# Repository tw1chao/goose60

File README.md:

# goose60

goose60 是一個 60% 鍵盤 PCB 電路板專案。
設計目標是做出一把**無光害的熱插拔鍵盤**，MCU 採用 ARM Cortex-M3 的 STM32F103。所有按鍵位置皆支援軸體熱插拔，本系列含子專案皆為無光害版本，故電路上僅會有的 `caps lock` 指示燈。

goose60 支援標準60%布局，下面表格列出子專案及支援的布局。

| Sub-Project | Layout |
|-------------|--------|
| JY60        | HHKB   |
| Cattle60    | ISO    |

未來視情況需要，再新增其他布局的子專案。

## 3D 預覽

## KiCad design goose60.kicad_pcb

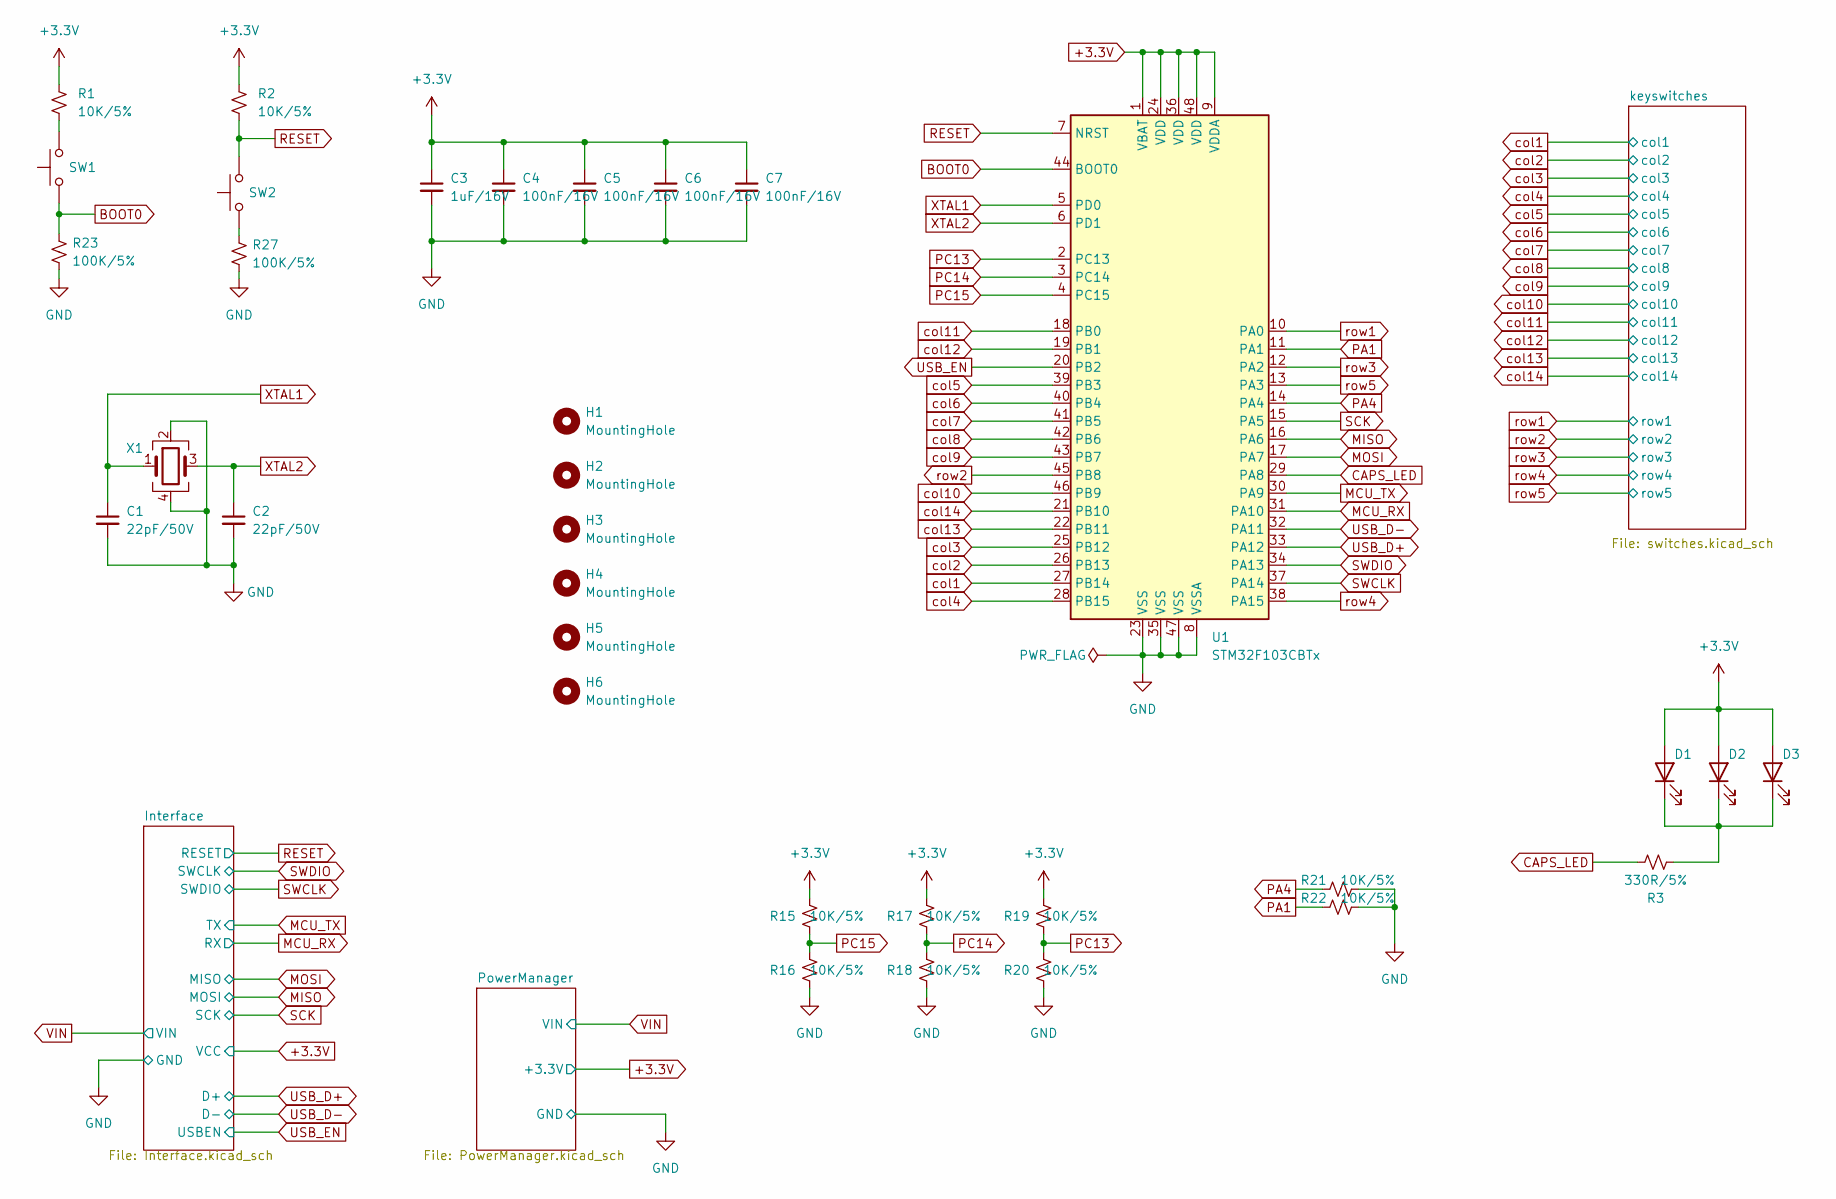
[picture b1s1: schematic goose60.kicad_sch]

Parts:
C1, C2: 22pF/50V; C_0603_1608Metric
C3: 1uF/16V; C_0603_1608Metric
C4, C5, C6, C7: 100nF/16V; C_0603_1608Metric
D1, D2, D3: LED; LED_0805_2012Metric
H1: MountingHole; MountingHole_3.2mm_M3_Pad
H2, H3, H4, H5, H6: MountingHole; MountingHole_3.2mm_M3_Pad_TopOnly
R1, R2, R15, R16, R17, R18, R19, R20, R21, R22: 10K/5%; R_0603_1608Metric
R3: 330R/5%; R_0603_1608Metric
R23, R27: 100K/5%; R_0603_1608Metric
SW1, SW2: SW_Push; SW_Push_1P1T_NO_CK_KSC6xxJ
U1: STM32F103CBTx; LQFP-48_7x7mm_P0.5mm
X1: Crystal_GND24; Crystal_SMD_TXC_7M-4Pin_3.2x2.5mm

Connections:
+3.3V: C3.1, C4.1, C5.1, C6.1, C7.1, D1.2 (A), D2.2 (A), D3.2 (A), R1.1, R2.1, R15.1, R17.1, R19.1, U1.1 (VBAT), U1.9 (VDDA), U1.24 (VDD), U1.36 (VDD), U1.48 (VDD); also elsewhere on the board
BOOT0: R23.1, SW1.1, U1.44 (BOOT0)
CAPS_LED: R3.2, U1.29 (PA8)
GND: C1.2, C2.2, C3.2, C4.2, C5.2, C6.2, C7.2, R16.2, R18.2, R20.2, R21.1, R22.1, R23.2, R27.2, U1.8 (VSSA), U1.23 (VSS), U1.35 (VSS), U1.47 (VSS), X1.2, X1.4; also elsewhere on the board
MCU_RX: U1.31 (PA10); also elsewhere on the board
MCU_TX: U1.30 (PA9); also elsewhere on the board
MISO: U1.16 (PA6); also elsewhere on the board
MOSI: U1.17 (PA7); also elsewhere on the board
unnamed: D1.1 (K), D2.1 (K), D3.1 (K), R3.1
unnamed: R1.2, SW1.2
unnamed: R27.1, SW2.1
PA1: R22.2, U1.11 (PA1)
PA4: R21.2, U1.14 (PA4)
PC13: R19.2, R20.1, U1.2 (PC13)
PC14: R17.2, R18.1, U1.3 (PC14)
PC15: R15.2, R16.1, U1.4 (PC15)
RESET: R2.2, SW2.2, U1.7 (NRST); also elsewhere on the board
SCK: U1.15 (PA5); also elsewhere on the board
SWCLK: U1.37 (PA14); also elsewhere on the board
SWDIO: U1.34 (PA13); also elsewhere on the board
USB_D+: U1.33 (PA12); also elsewhere on the board
USB_D-: U1.32 (PA11); also elsewhere on the board
USB_EN: U1.20 (PB2); also elsewhere on the board
XTAL1: C1.1, U1.5 (PD0), X1.1
XTAL2: C2.1, U1.6 (PD1), X1.3
col1: U1.27 (PB14); also elsewhere on the board
col2: U1.26 (PB13); also elsewhere on the board
col3: U1.25 (PB12); also elsewhere on the board
col4: U1.28 (PB15); also elsewhere on the board
col5: U1.39 (PB3); also elsewhere on the board
col6: U1.40 (PB4); also elsewhere on the board
col7: U1.41 (PB5); also elsewhere on the board
col8: U1.42 (PB6); also elsewhere on the board
col9: U1.43 (PB7); also elsewhere on the board
col10: U1.46 (PB9); also elsewhere on the board
col11: U1.18 (PB0); also elsewhere on the board
col12: U1.19 (PB1); also elsewhere on the board
col13: U1.22 (PB11); also elsewhere on the board
col14: U1.21 (PB10); also elsewhere on the board
row1: U1.10 (PA0); also elsewhere on the board
row2: U1.45 (PB8); also elsewhere on the board
row3: U1.12 (PA2); also elsewhere on the board
row4: U1.38 (PA15); also elsewhere on the board
row5: U1.13 (PA3); also elsewhere on the board

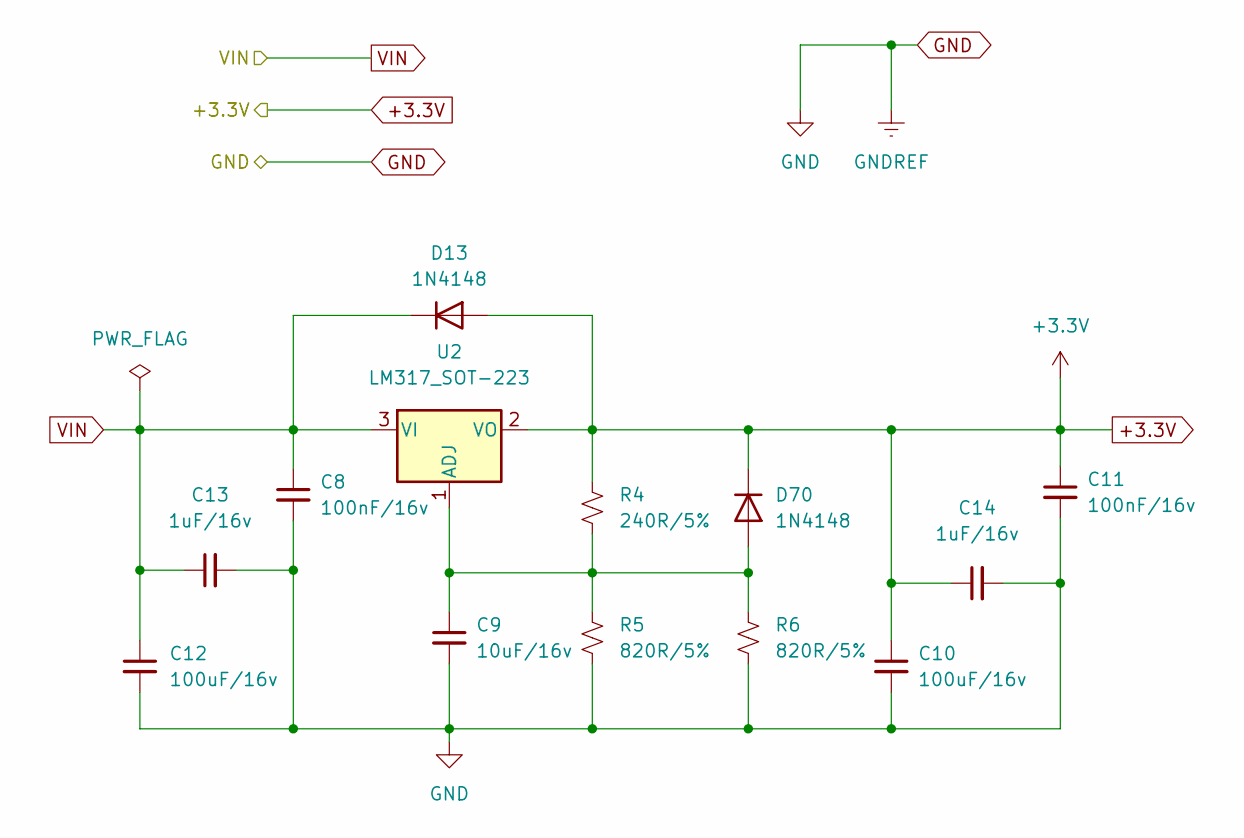
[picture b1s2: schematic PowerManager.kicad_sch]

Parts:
C8, C11: 100nF/16v; C_0603_1608Metric
C9: 10uF/16v; C_0805_2012Metric
C10, C12: 100uF/16v; C_1206_3216Metric
C13, C14: 1uF/16v; C_0603_1608Metric
D13, D70: 1N4148; D_0805_2012Metric
R4: 240R/5%; R_0603_1608Metric
R5, R6: 820R/5%; R_0603_1608Metric
U2: LM317_SOT-223; SOT-223-3_TabPin2

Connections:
+3.3V: C10.1, C11.1, C14.1, D13.2 (A), D70.1 (K), R4.1, U2.2 (VO); also elsewhere on the board
GND: C8.2, C9.2, C10.2, C11.2, C12.2, C13.2, C14.2, R5.2, R6.2; also elsewhere on the board
unnamed: C9.1, D70.2 (A), R4.2, R5.1, R6.1, U2.1 (ADJ)
VIN: C8.1, C12.1, C13.1, D13.1 (K), U2.3 (VI); also elsewhere on the board

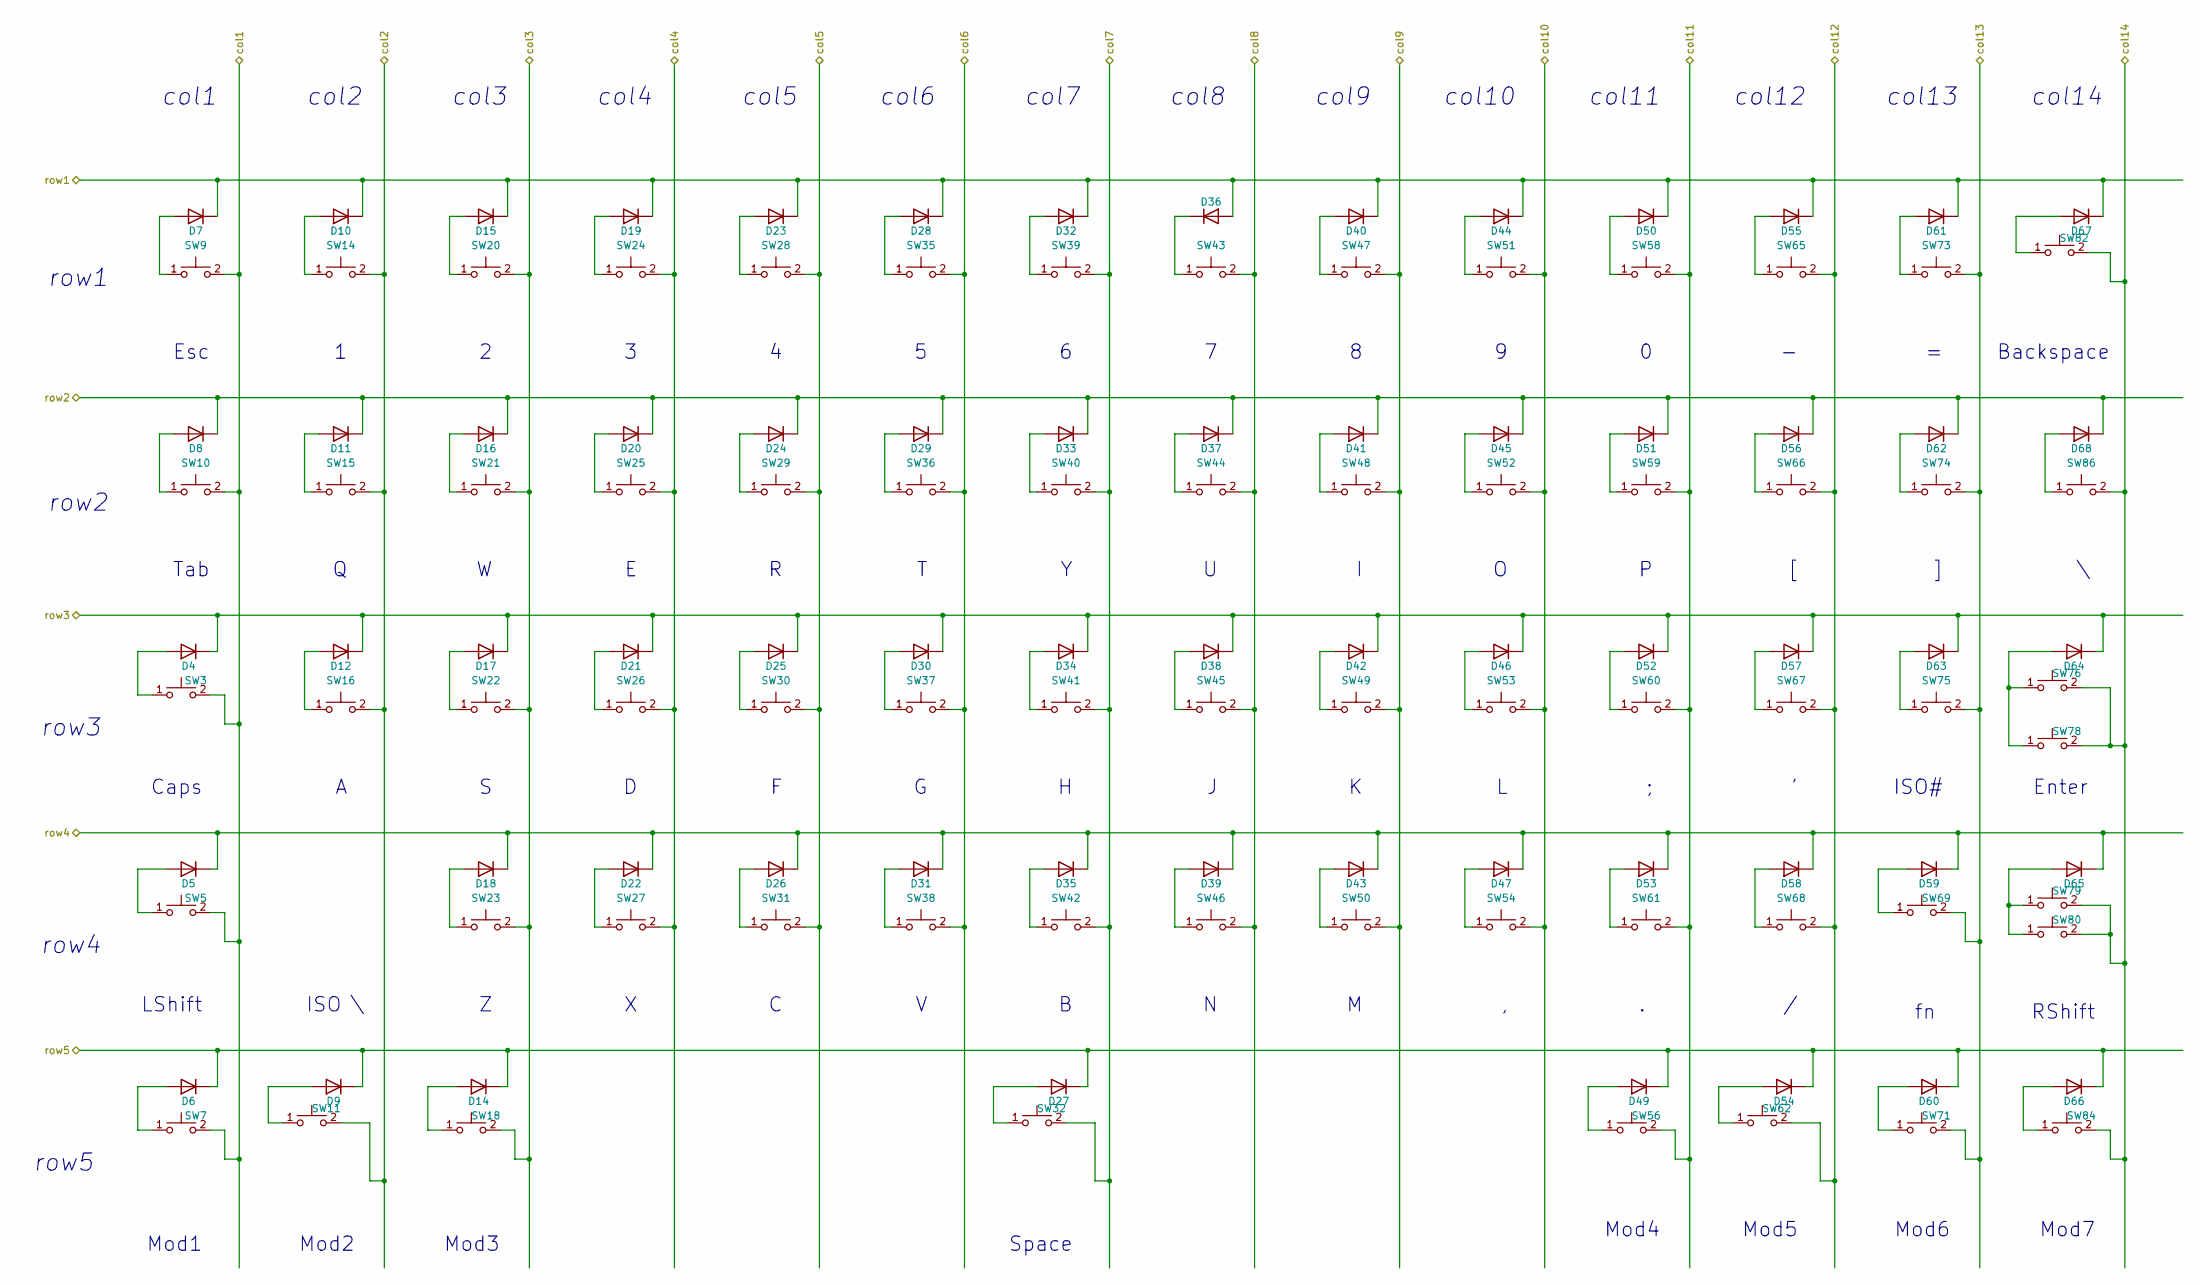
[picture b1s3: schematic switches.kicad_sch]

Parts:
D4, D5, D6, D7, D8, D9, D10, D11, D12, D14, D15, D16, D17, D18, D19, D20, D21, D22, D23, D24, D25, D26, D27, D28, D29, D30, D31, D32, D33, D34, D35, D36, D37, D38, D39, D40, D41, D42, D43, D44, D45, D46, D47, D49, D50, D51, D52, D53, D54, D55, D56, D57, D58, D59, D60, D61, D62, D63, D64, D65, D66, D67, D68: 1N4148; D_0805_2012Metric
SW3, SW5, SW7, SW9, SW10, SW11, SW14, SW15, SW16, SW18, SW20, SW21, SW22, SW23, SW24, SW25, SW26, SW27, SW28, SW29, SW30, SW31, SW32, SW35, SW36, SW37, SW38, SW39, SW40, SW41, SW42, SW43, SW44, SW45, SW46, SW47, SW48, SW49, SW50, SW51, SW52, SW53, SW54, SW56, SW58, SW59, SW60, SW61, SW62, SW65, SW66, SW67, SW68, SW69, SW71, SW73, SW74, SW75, SW76, SW78, SW79, SW80, SW82, SW84, SW86: SW_Push; Kailh_socket_MX

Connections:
unnamed: D4.2 (A), SW3.1
unnamed: D5.2 (A), SW5.1
unnamed: D6.2 (A), SW7.1
unnamed: D7.2 (A), SW9.1
unnamed: D8.2 (A), SW10.1
unnamed: D9.2 (A), SW11.1
unnamed: D10.2 (A), SW14.1
unnamed: D11.2 (A), SW15.1
unnamed: D12.2 (A), SW16.1
unnamed: D14.2 (A), SW18.1
unnamed: D15.2 (A), SW20.1
unnamed: D16.2 (A), SW21.1
unnamed: D17.2 (A), SW22.1
unnamed: D18.2 (A), SW23.1
unnamed: D19.2 (A), SW24.1
unnamed: D20.2 (A), SW25.1
unnamed: D21.2 (A), SW26.1
unnamed: D22.2 (A), SW27.1
unnamed: D23.2 (A), SW28.1
unnamed: D24.2 (A), SW29.1
unnamed: D25.2 (A), SW30.1
unnamed: D26.2 (A), SW31.1
unnamed: D27.2 (A), SW32.1
unnamed: D28.2 (A), SW35.1
unnamed: D29.2 (A), SW36.1
unnamed: D30.2 (A), SW37.1
unnamed: D31.2 (A), SW38.1
unnamed: D32.2 (A), SW39.1
unnamed: D33.2 (A), SW40.1
unnamed: D34.2 (A), SW41.1
unnamed: D35.2 (A), SW42.1
unnamed: D36.1 (K), SW43.1
unnamed: D37.2 (A), SW44.1
unnamed: D38.2 (A), SW45.1
unnamed: D39.2 (A), SW46.1
unnamed: D40.2 (A), SW47.1
unnamed: D41.2 (A), SW48.1
unnamed: D42.2 (A), SW49.1
unnamed: D43.2 (A), SW50.1
unnamed: D44.2 (A), SW51.1
unnamed: D45.2 (A), SW52.1
unnamed: D46.2 (A), SW53.1
unnamed: D47.2 (A), SW54.1
unnamed: D49.2 (A), SW56.1
unnamed: D50.2 (A), SW58.1
unnamed: D51.2 (A), SW59.1
unnamed: D52.2 (A), SW60.1
unnamed: D53.2 (A), SW61.1
unnamed: D54.2 (A), SW62.1
unnamed: D55.2 (A), SW65.1
unnamed: D56.2 (A), SW66.1
unnamed: D57.2 (A), SW67.1
unnamed: D58.2 (A), SW68.1
unnamed: D59.2 (A), SW69.1
unnamed: D60.2 (A), SW71.1
unnamed: D61.2 (A), SW73.1
unnamed: D62.2 (A), SW74.1
unnamed: D63.2 (A), SW75.1
unnamed: D64.2 (A), SW76.1, SW78.1
unnamed: D65.2 (A), SW79.1, SW80.1
unnamed: D66.2 (A), SW84.1
unnamed: D67.2 (A), SW82.1
unnamed: D68.2 (A), SW86.1
col1: SW3.2, SW5.2, SW7.2, SW9.2, SW10.2; also elsewhere on the board
col2: SW11.2, SW14.2, SW15.2, SW16.2; also elsewhere on the board
col3: SW18.2, SW20.2, SW21.2, SW22.2, SW23.2; also elsewhere on the board
col4: SW24.2, SW25.2, SW26.2, SW27.2; also elsewhere on the board
col5: SW28.2, SW29.2, SW30.2, SW31.2; also elsewhere on the board
col6: SW35.2, SW36.2, SW37.2, SW38.2; also elsewhere on the board
col7: SW32.2, SW39.2, SW40.2, SW41.2, SW42.2; also elsewhere on the board
col8: SW43.2, SW44.2, SW45.2, SW46.2; also elsewhere on the board
col9: SW47.2, SW48.2, SW49.2, SW50.2; also elsewhere on the board
col10: SW51.2, SW52.2, SW53.2, SW54.2; also elsewhere on the board
col11: SW56.2, SW58.2, SW59.2, SW60.2, SW61.2; also elsewhere on the board
col12: SW62.2, SW65.2, SW66.2, SW67.2, SW68.2; also elsewhere on the board
col13: SW69.2, SW71.2, SW73.2, SW74.2, SW75.2; also elsewhere on the board
col14: SW76.2, SW78.2, SW79.2, SW80.2, SW82.2, SW84.2, SW86.2; also elsewhere on the board
row1: D7.1 (K), D10.1 (K), D15.1 (K), D19.1 (K), D23.1 (K), D28.1 (K), D32.1 (K), D36.2 (A), D40.1 (K), D44.1 (K), D50.1 (K), D55.1 (K), D61.1 (K), D67.1 (K); also elsewhere on the board
row2: D8.1 (K), D11.1 (K), D16.1 (K), D20.1 (K), D24.1 (K), D29.1 (K), D33.1 (K), D37.1 (K), D41.1 (K), D45.1 (K), D51.1 (K), D56.1 (K), D62.1 (K), D68.1 (K); also elsewhere on the board
row3: D4.1 (K), D12.1 (K), D17.1 (K), D21.1 (K), D25.1 (K), D30.1 (K), D34.1 (K), D38.1 (K), D42.1 (K), D46.1 (K), D52.1 (K), D57.1 (K), D63.1 (K), D64.1 (K); also elsewhere on the board
row4: D5.1 (K), D18.1 (K), D22.1 (K), D26.1 (K), D31.1 (K), D35.1 (K), D39.1 (K), D43.1 (K), D47.1 (K), D53.1 (K), D58.1 (K), D59.1 (K), D65.1 (K); also elsewhere on the board
row5: D6.1 (K), D9.1 (K), D14.1 (K), D27.1 (K), D49.1 (K), D54.1 (K), D60.1 (K), D66.1 (K); also elsewhere on the board

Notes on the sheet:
col1
ISO#
col3
ISO \
Mod2
row1
col9
col6
Mod3
Mod7
col13
col4
Backspace
col14
col11
col12
Mod5
RShift
row3
LShift
row5
col10
Mod1
Space
Esc
col5
col7
Caps
col8
Mod6
col2
Enter
row2
row4
Mod4
Tab

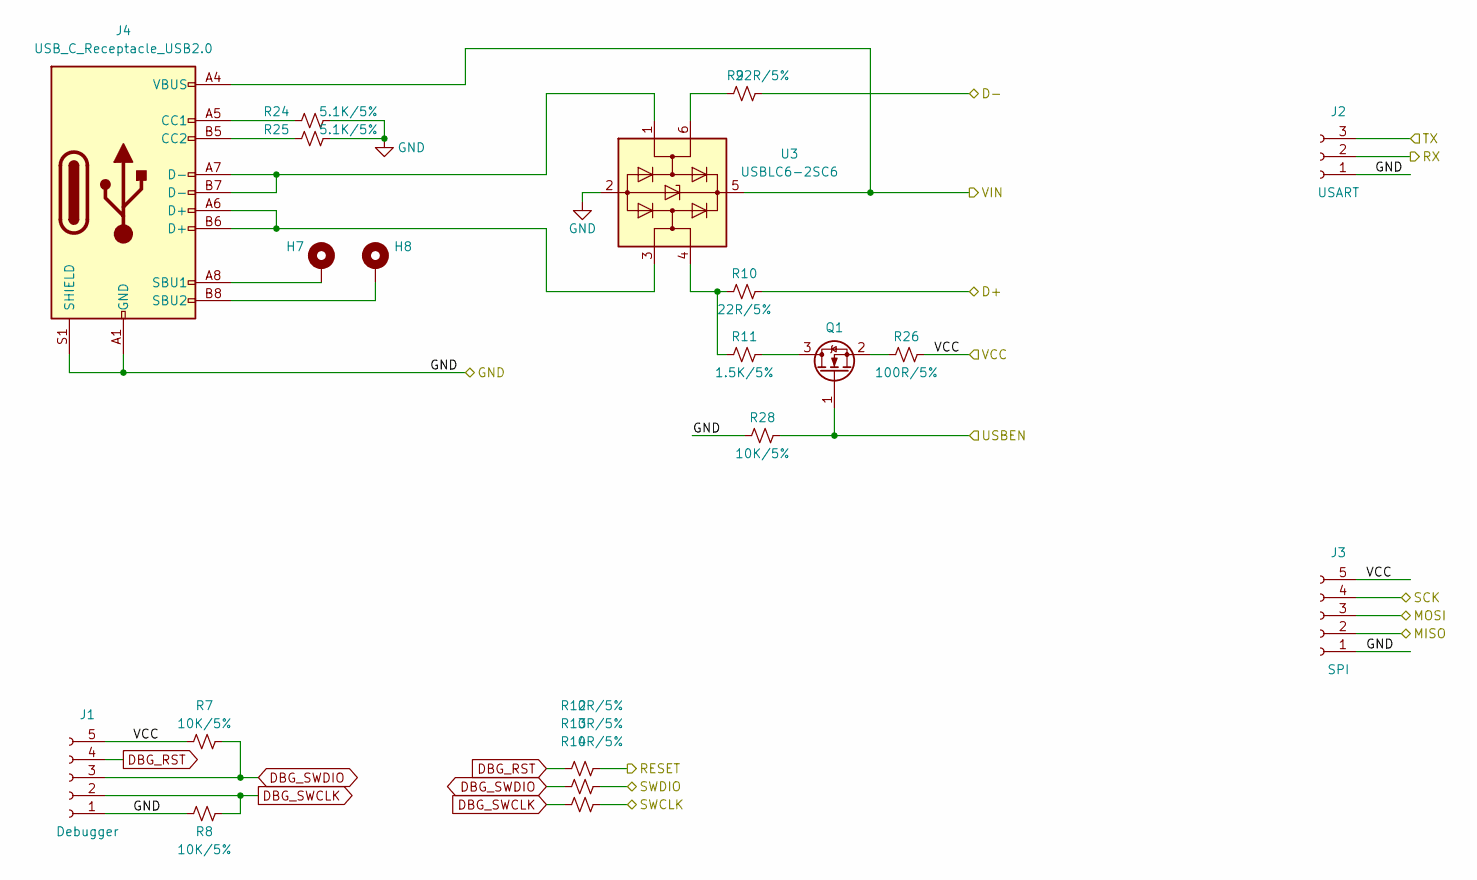
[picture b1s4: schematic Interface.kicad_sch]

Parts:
H7, H8: MountingHole_Pad; NetTie-2_SMD_Pad0.5mm
J1: Debugger; PinHeader_1x05_P2.00mm_Vertical
J2: USART; PinHeader_1x03_P2.00mm_Vertical
J3: SPI; PinHeader_1x05_P2.00mm_Vertical
J4: USB_C_Receptacle_USB2.0; USB_C_Receptacle_HRO_TYPE-C-31-M-12
Q1: Q_NMOS_GSD; SOT-23
R7, R8, R28: 10K/5%; R_0603_1608Metric
R9, R10: 22R/5%; R_0603_1608Metric
R11: 1.5K/5%; R_0603_1608Metric
R12, R13, R14: 0R/5%; R_0603_1608Metric
R24, R25: 5.1K/5%; R_0603_1608Metric
R26: 100R/5%; R_0603_1608Metric
U3: USBLC6-2SC6; SOT-23-6

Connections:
+3.3V: J1.5, J3.5, R7.1, R26.2; also elsewhere on the board
DBG_RST: J1.4, R12.1
DBG_SWCLK: J1.2, R8.2, R14.1
DBG_SWDIO: J1.3, R7.2, R13.1
GND: J1.1, J2.1, J3.1, J4.A1 (GND), J4.A12 (GND), J4.B1 (GND), J4.B12 (GND), J4.S1 (SHIELD), R8.1, R24.2, R25.2, R28.1, U3.2 (GND); also elsewhere on the board
MCU_RX: J2.2; also elsewhere on the board
MCU_TX: J2.3; also elsewhere on the board
MISO: J3.3; also elsewhere on the board
MOSI: J3.2; also elsewhere on the board
unnamed: H7.1, J4.A8 (SBU1)
unnamed: H8.1, J4.B8 (SBU2)
unnamed: J4.A5 (CC1), R24.1
unnamed: J4.A6 (D+), J4.B6 (D+), U3.3 (I/O2)
unnamed: J4.A7 (D-), J4.B7 (D-), U3.1 (I/O1)
unnamed: J4.B5 (CC2), R25.1
unnamed: Q1.2 (S), R26.1
unnamed: Q1.3 (D), R11.2
unnamed: R9.1, U3.6 (I/O1)
unnamed: R10.1, R11.1, U3.4 (I/O2)
RESET: R12.2; also elsewhere on the board
SCK: J3.4; also elsewhere on the board
SWCLK: R13.2; also elsewhere on the board
SWDIO: R14.2; also elsewhere on the board
USB_D+: R10.2; also elsewhere on the board
USB_D-: R9.2; also elsewhere on the board
USB_EN: Q1.1 (G), R28.2; also elsewhere on the board
VIN: J4.A4 (VBUS), J4.A9 (VBUS), J4.B4 (VBUS), J4.B9 (VBUS), U3.5 (VBUS); also elsewhere on the board

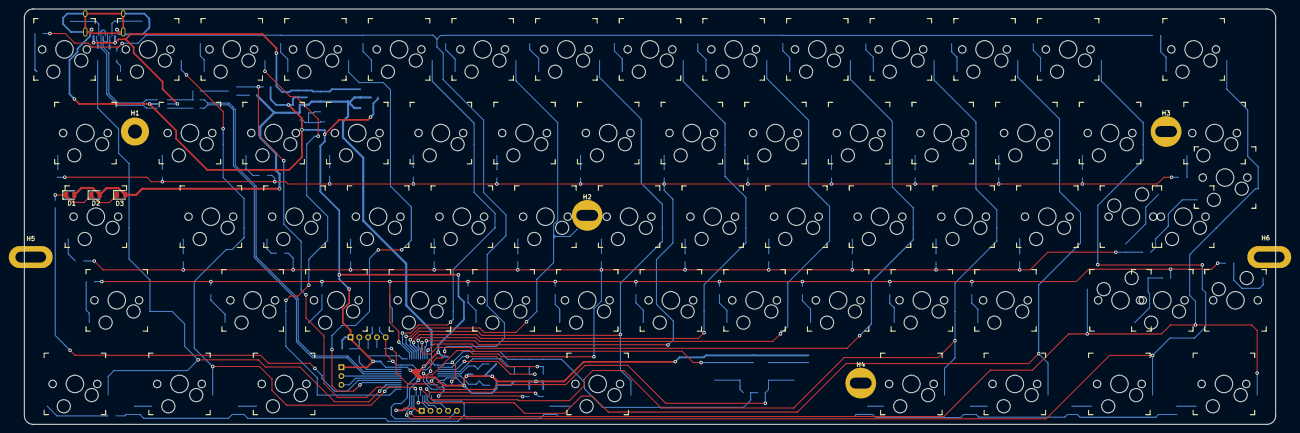
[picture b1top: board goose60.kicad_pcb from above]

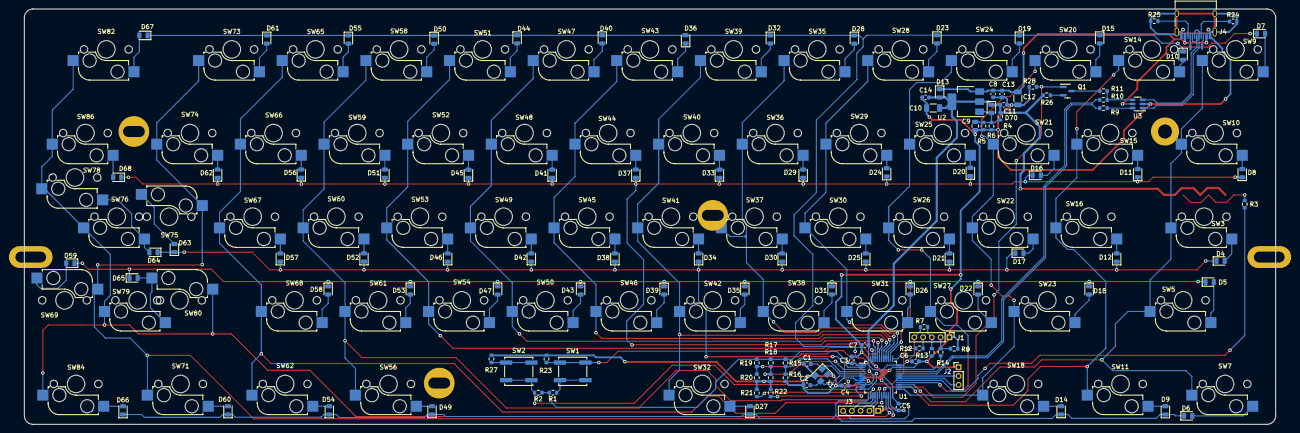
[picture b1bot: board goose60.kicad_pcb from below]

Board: 2 copper layers, 285.0 x 94.6 mm, 194 parts (120 on the bottom side), 122 nets.

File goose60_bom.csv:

"ID";"指示符";"軟體包";"數量";"名稱";"供應商和參考";
1;"SW53,SW5,SW71,SW22,SW3,SW10,SW78,SW11,SW52,SW20,SW61,SW27,SW35,SW76,SW9,SW65,SW29,SW37,SW41,SW23,SW21,SW82,SW79,SW58,SW67,SW25,SW18,SW59,SW46,SW28,SW43,SW16,SW15,SW7,SW31,SW39,SW75,SW73,SW54,SW60,SW69,SW32,SW44,SW30,SW47,SW84,SW38,SW80,SW45,SW74,SW86,SW40,SW66,SW24,SW50,SW62,SW42,SW48,SW56,SW51,SW49,SW26,SW14,SW36,SW68";"Kailh_socket_MX";65;"SW_Push";;;
2;"H6,H4,H2,H3,H5,H1";"MountingHole_3.2mm_M3_Pad_TopOnly";6;"MountingHole";;;
3;"D1";"LED_0805_2012Metric";1;"LED";;;
4;"C14,C13";"C_0603_1608Metric";2;"1uF/16v";;;
5;"D36,D8,D32,D61,D20,D59,D42,D52,D12,D44,D37,D62,D10,D5,D60,D43,D65,D55,D9,D49,D39,D30,D54,D50,D7,D28,D67,D6,D41,D25,D21,D64,D58,D68,D35,D57,D26,D15,D16,D24,D47,D27,D51,D33,D40,D14,D13,D18,D46,D38,D17,D23,D19,D11,D22,D66,D29,D45,D53,D4,D34,D63,D31,D70,D56";"D_0805_2012Metric";65;"1N4148";;;
6;"H8,H7";"NetTie-2_SMD_Pad0.5mm";2;"MountingHole_Pad";;;
7;"R27,R23";"R_0603_1608Metric";2;"100K/5%";;;
8;"C7,C5,C6,C4";"C_0603_1608Metric";4;"100nF/16V";;;
9;"SW1,SW2";"SW_Push_1P1T_NO_CK_KSC6xxJ";2;"SW_Push";;;
10;"R3";"R_0603_1608Metric";1;"330R/5%";;;
11;"R24,R25";"R_0603_1608Metric";2;"5.1K/5%";;;
12;"R10,R9";"R_0603_1608Metric";2;"22R/5%";;;
13;"C1,C2";"C_0603_1608Metric";2;"22pF/50V";;;
14;"C3";"C_0603_1608Metric";1;"1uF/16V";;;
15;"R11,R8,R22,R17,R7,R2,R15,R21,R19,R1";"R_0603_1608Metric";10;"10K/5%";;;
16;"R4";"R_0603_1608Metric";1;"240R/5%";;;
17;"J1";"PinHeader_1x05_P2.00mm_Vertical";1;"Debugger";;;
18;"R13";"R_0603_1608Metric";1;"1.5K/5%";;;
19;"C11,C8";"C_0603_1608Metric";2;"100nF/16v";;;
20;"R5,R6";"R_0603_1608Metric";2;"820R/5%";;;
21;"C9";"C_0805_2012Metric";1;"10uF/16v";;;
22;"U1";"LQFP-48_7x7mm_P0.5mm";1;"STM32F103CBTx";;;
23;"J3";"PinHeader_1x05_P2.00mm_Vertical";1;"SPI";;;
24;"C12,C10";"C_1206_3216Metric";2;"100uF/16v";;;
25;"J4";"USB_C_Receptacle_HRO_TYPE-C-31-M-12";1;"USB_C_Receptacle_USB2.0";;;
26;"R12";"R_0603_1608Metric";1;"0R/5%";;;
27;"X1";"Crystal_SMD_TXC_7M-4Pin_3.2x2.5mm";1;"Crystal_GND24";;;
28;"U3";"SOT-23-6";1;"USBLC6-2SC6";;;
29;"J2";"PinHeader_1x03_P2.00mm_Vertical";1;"USART";;;
30;"U2";"SOT-223-3_TabPin2";1;"LM317_SOT-223";;;

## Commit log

2022-07-15 init project
2022-07-18 add gh60 lib to project
2022-07-30 add kailh socket lib submodule
2022-07-31 clean goose60 project re-defined sch
2022-07-31 init new project
2022-07-31 add keyswitch submodule
2022-07-31 add new design
2022-08-01 update goose60 sch footprint
2022-08-02 update footpoint and add pcb layout
2022-08-02 update diode location
2022-08-03 remove key
2022-08-03 update components location
2022-08-04 add HOLE
2022-08-05 update MX socket loaction
2022-08-06 add res and fix rule check fail problom
2022-08-07 change pin default and try layout
2022-08-08 update pcb layout and pin defined
2022-08-09 add usb enable pin
2022-08-09 add gh60 mechanism hole
2022-08-10 update MCU VCC and GND layout
2022-08-10 fix pcb edge cuts link error
2022-08-13 fix usb type-c location
2022-08-15 modify power/bootload circuit
2022-08-17 modify pcb footprint
2022-08-18 change Diode direction and update PR #1 footprint
2022-08-18 create license
2022-08-19 fix layout rule error and warring
2022-08-20 fix diode direction on row1
2022-08-24 update pcb layout
2022-08-25 update pcb layout and add GND via
2022-08-26 update XTAL ground via and layout
2022-08-27 clean pcb layer and add readme file
    * BOM
    * layout
    * pcb PDF file
    * sch PDF file
2022-08-28 add iso layout "iso /" key
2022-08-28 remove ISO layout
    * iso layout fork to cattle60 project
2022-08-30 change switch lib
2022-08-30 update keyswitch foodpoint
2022-08-30 clean docs/
2022-08-30 remove switches.pretty library
2022-08-30 update 3D picture
2022-08-31 change MCU location and change row5 pin
    * row5 -> PB2
2022-09-01 modify layout lines
2022-09-01 change LDO ic and PCB layout
2022-09-02 modify crystal layout and add keyswitch & USBC 3D module
2022-09-02 modify usb layout and add text to pcb
2022-09-07 Add BOM list
2022-09-08 modify power manager value
2022-09-28 update BOM
2022-10-15 update keyboard 3D object to PCB
2022-10-15 update doc images
